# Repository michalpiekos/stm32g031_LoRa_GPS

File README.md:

# stm32g031_LoRa_GPS
GPS position transmitter using LoRa. Based on STM32G031 controller with HAL and Makefile.

## Testing
In current development stage it is still testing rig.
I have included SSD1306 Oled for debugging in the field.
Included PCB design made in KiCAD. <br />

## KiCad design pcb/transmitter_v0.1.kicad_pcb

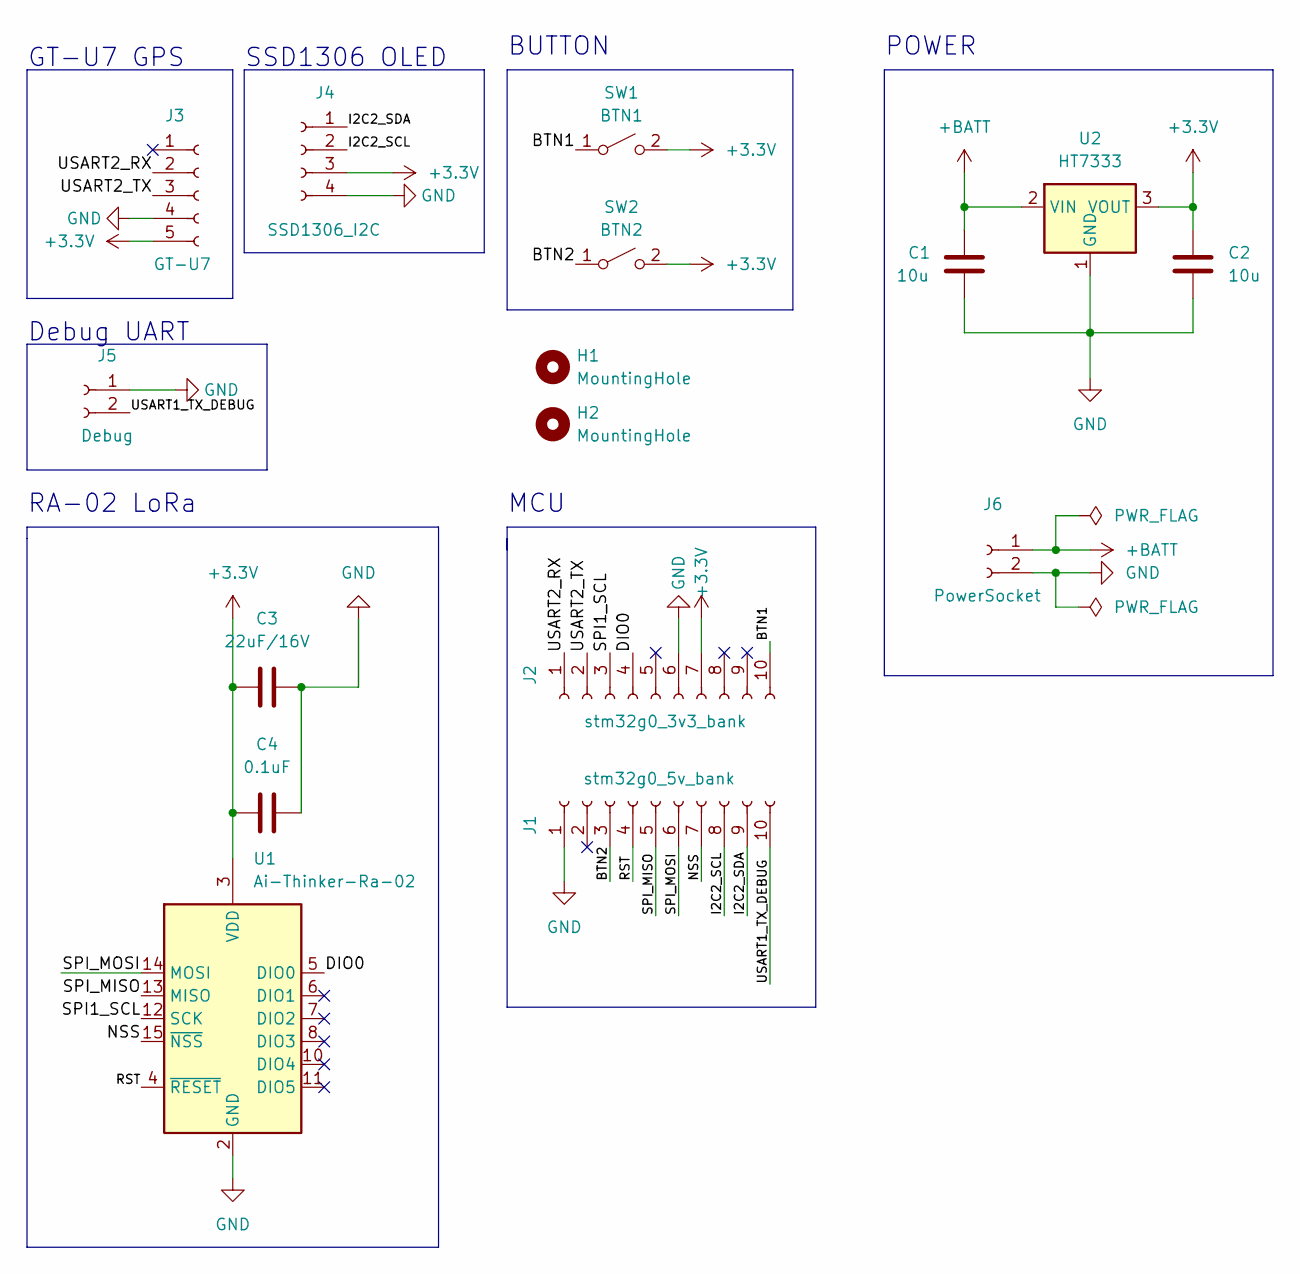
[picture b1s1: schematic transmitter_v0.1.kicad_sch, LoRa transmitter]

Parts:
C1, C2: 10u; C_0805_2012Metric_Pad1.18x1.45mm_HandSolder
C3: 22uF/16V; C_0805_2012Metric_Pad1.18x1.45mm_HandSolder
C4: 0.1uF; C_0805_2012Metric_Pad1.18x1.45mm_HandSolder
H1, H2: MountingHole; MountingHole_3.2mm_M3_DIN965_Pad_TopBottom
J1: stm32g0_5v_bank; PinHeader_1x10_P2.54mm_Vertical
J2: stm32g0_3v3_bank; PinHeader_1x10_P2.54mm_Vertical
J3: GT-U7; PinHeader_1x05_P2.54mm_Vertical
J4: SSD1306_I2C; PinSocket_1x04_P2.54mm_Vertical
J5: Debug; PinHeader_1x02_P2.54mm_Vertical
J6: PowerSocket; PinHeader_1x02_P2.54mm_Vertical
SW1: BTN1; SW_PUSH_6mm
SW2: BTN2; SW_PUSH_6mm
U1: Ai-Thinker-Ra-02; Ai-Thinker-Ra-01-LoRa
U2: HT7333; SOT-89-3_Handsoldering

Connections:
+3.3V: C2.1, C3.1, C4.1, J2.7, J3.5, J4.3, SW1.2 (B), SW2.2 (B), U1.3 (VDD), U2.3 (VOUT)
+BATT: C1.1, J6.1, U2.2 (VIN)
/BTN1: J2.10, SW1.1 (A)
/BTN2: J1.3, SW2.1 (A)
/DIO0: J2.4, U1.5 (DIO0)
/I2C2_SCL: J1.8, J4.2
/I2C2_SDA: J1.9, J4.1
/NSS: J1.7, U1.15 (~NSS)
/RST: J1.4, U1.4 (~RESET)
/SPI1_SCL: J2.3, U1.12 (SCK)
/SPI_MISO: J1.5, U1.13 (MISO)
/SPI_MOSI: J1.6, U1.14 (MOSI)
/USART1_TX_DEBUG: J1.10, J5.2
/USART2_RX: J2.1, J3.2
/USART2_TX: J2.2, J3.3
GND: C1.2, C2.2, C3.2, C4.2, J1.1, J2.6, J3.4, J4.4, J5.1, J6.2, U1.1 (GND), U1.2 (GND), U1.9 (GND), U1.16 (GND), U2.1 (GND)

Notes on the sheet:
MCU
GT-U7 GPS
Debug UART
POWER
BUTTON
SSD1306 OLED
RA-02 LoRa

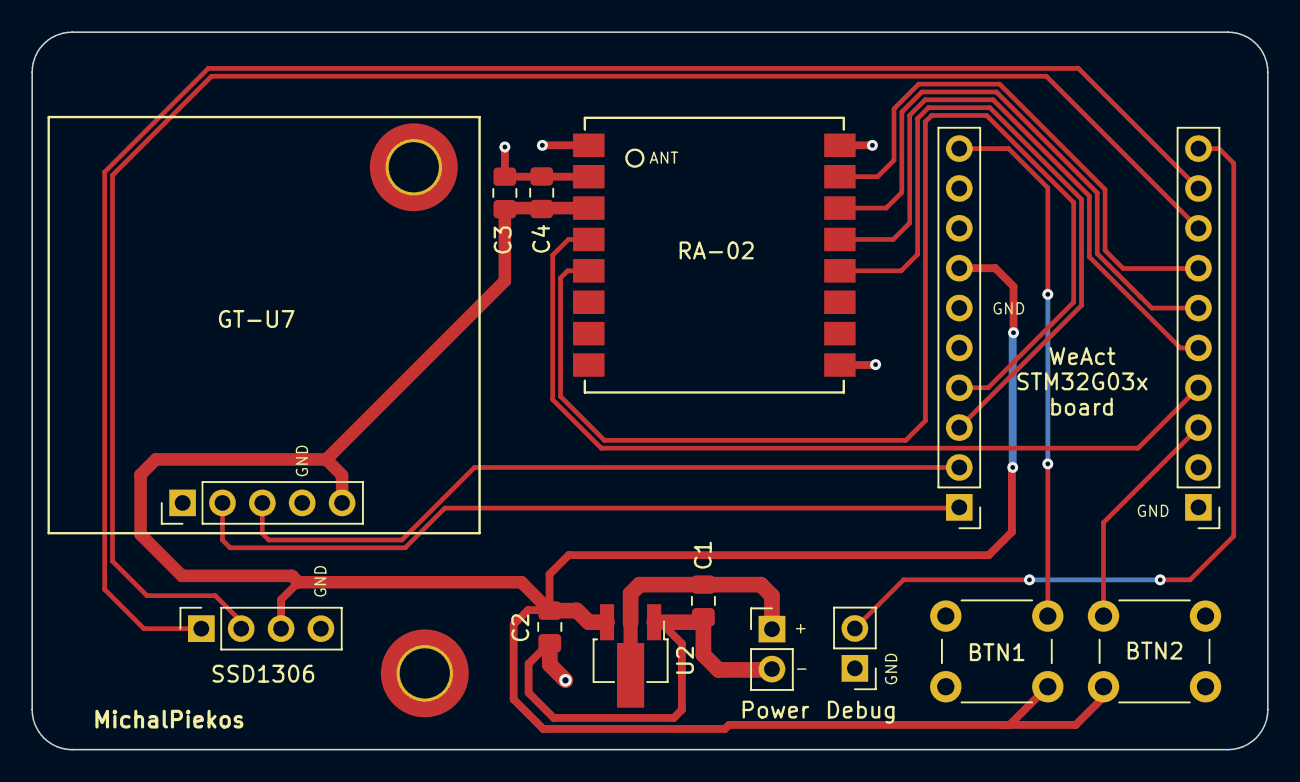
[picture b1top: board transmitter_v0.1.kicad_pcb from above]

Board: 2 copper layers, 78.7 x 45.7 mm, 16 parts (0 on the bottom side), 16 nets.

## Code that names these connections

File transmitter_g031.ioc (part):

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Mcu.Name=STM32G031F(4-6-8)Px
Mcu.Package=TSSOP20
Mcu.UserName=STM32G031F8Px
PA0.GPIOParameters=GPIO_Label
PA0.GPIO_Label=DIO0
PA0.Signal=GPXTI0
PA1.Mode=Full_Duplex_Master
PA1.Signal=SPI1_SCK
PA11\ [PA9].Mode=I2C
PA11\ [PA9].Signal=I2C2_SCL
PA12\ [PA10].Mode=I2C
PA12\ [PA10].Signal=I2C2_SDA
PA13.Mode=Serial_Wire
PA13.Signal=SYS_SWDIO
PA14-BOOT0.Mode=Serial_Wire
PA14-BOOT0.Signal=SYS_SWCLK
PA14-BOOT0__PA15.StandardMode=true
PA2.Mode=Asynchronous
PA2.Signal=USART2_TX
PA3.Mode=Asynchronous
PA3.Signal=USART2_RX
PA4.GPIOParameters=GPIO_PuPd,GPIO_Label
PA4.GPIO_Label=BTN1
PA4.GPIO_PuPd=GPIO_PULLDOWN
PA4.Signal=GPXTI4
PA5.GPIOParameters=GPIO_Label
PA5.GPIO_Label=RST
PA5.Signal=GPIO_Output
PA6.Mode=Full_Duplex_Master
PA6.Signal=SPI1_MISO
PA7.Mode=Full_Duplex_Master
PA7.Signal=SPI1_MOSI
PA8.GPIOParameters=GPIO_Label
PA8.GPIO_Label=NSS
PA8.Signal=GPIO_Output
PB0__PB1__PB2__PA8.StandardMode=true
PB3__PB4__PB5__PB6.StandardMode=true
PB6.Mode=Half_duplex(single_wire_mode)
PB6.Signal=USART1_TX
PB7.GPIOParameters=GPIO_PuPd,GPIO_Label
PB7.GPIO_Label=BTN2
PB7.GPIO_PuPd=GPIO_PULLDOWN
PB7.Signal=GPXTI7
PB7__PB8.StandardMode=true
PC14-OSC32_IN\ (PC14)__PB9.StandardMode=true
RCC.HSE_VALUE=8000000
RCC.SYSCLKFreq_VALUE=64000000
RCC.SYSCLKSource=RCC_SYSCLKSOURCE_PLLCLK
board=custom

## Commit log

2023-11-15 description change
